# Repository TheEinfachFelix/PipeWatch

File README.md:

# PipeWatch

## Sensors

- MSU: LIS3DHTR 
- WS2812B
- Taster (Implementiert)
- Temp: 2x DS18B20(UMW) (Implementiert)
- ADC: ADS1115IDGSR (Implementiert)

## Todos

- Umrechnung der Werte in echte einheiten
- Dashboard für mehrere Geräte

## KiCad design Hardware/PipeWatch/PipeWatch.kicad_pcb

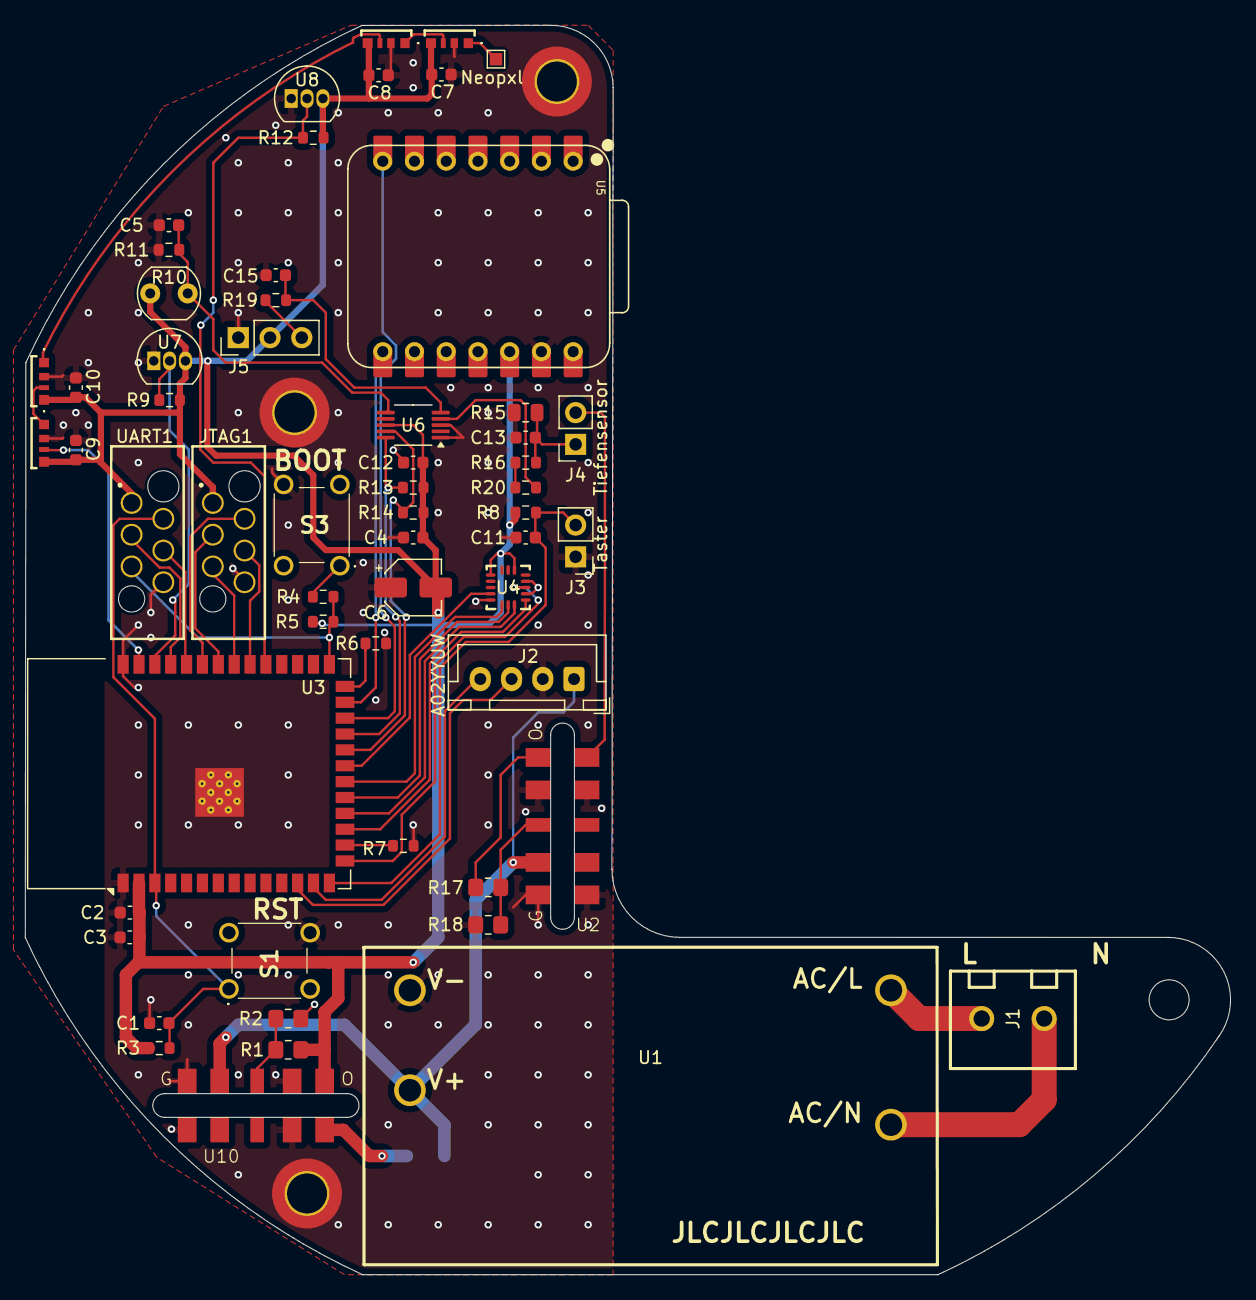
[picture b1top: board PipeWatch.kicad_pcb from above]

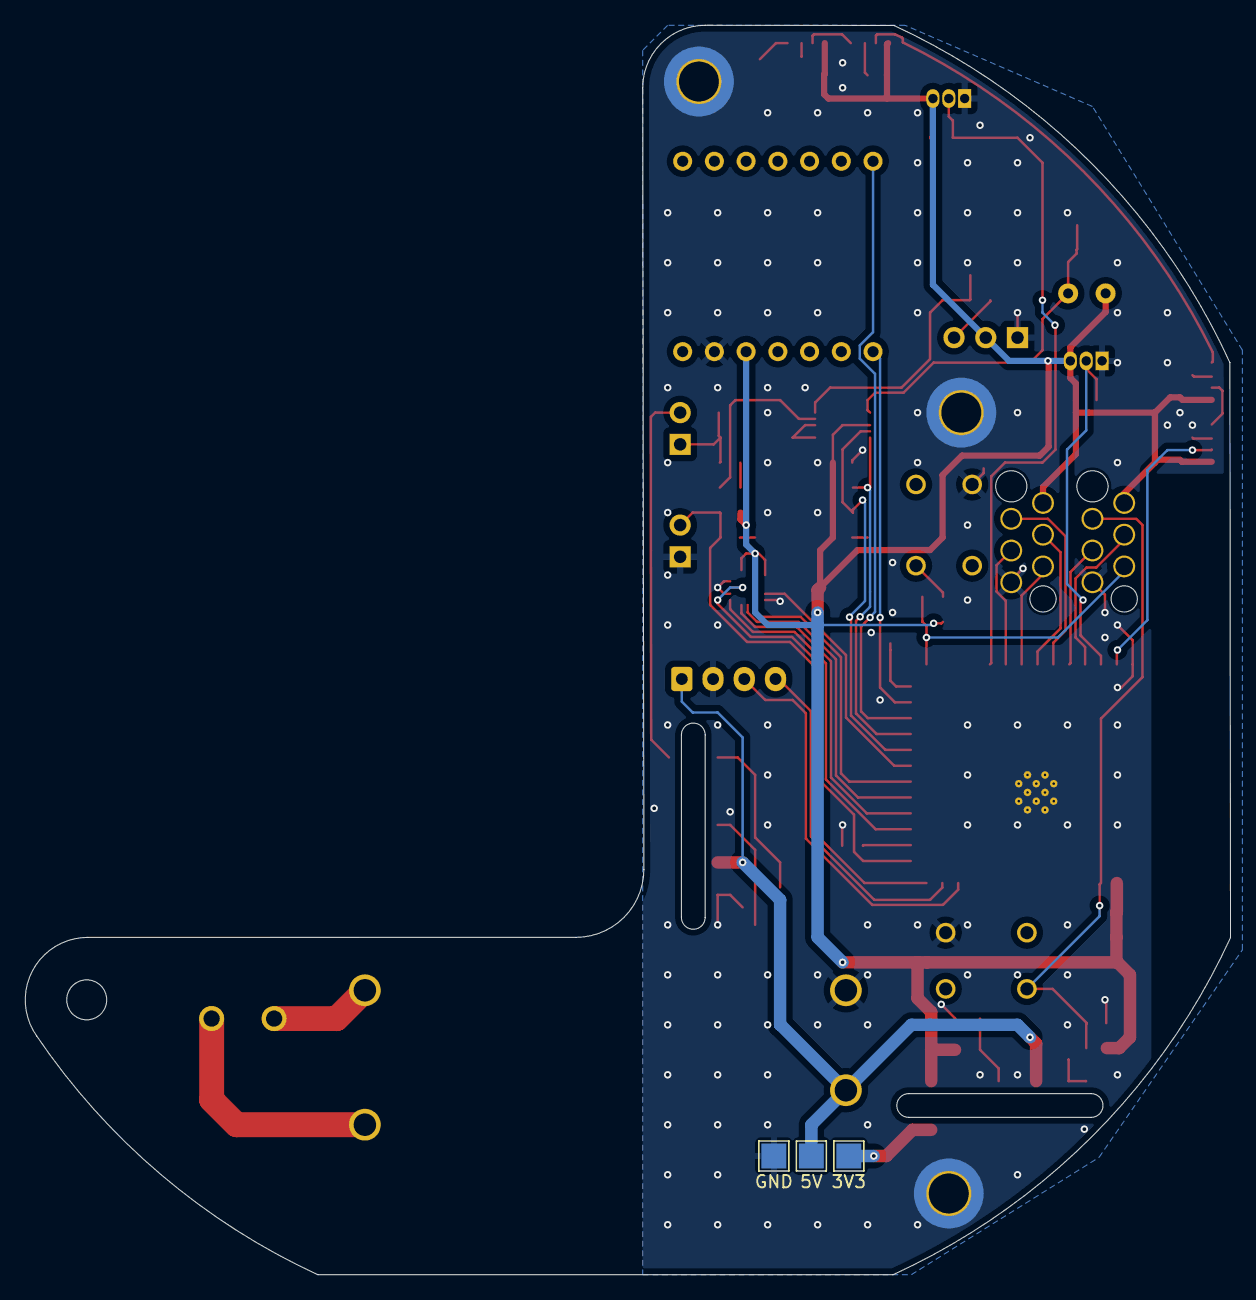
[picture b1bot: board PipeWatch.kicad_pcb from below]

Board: 2 copper layers, 96.5 x 100.0 mm, 64 parts (3 on the bottom side), 45 nets.

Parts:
C1, C2, C4, C7, C8, C9, C10, C11, C12: 100n; C_0603_1608Metric
C3: 22u; C_0603_1608Metric
C5, C13, C15: 10n; C_0603_1608Metric
C6: 10u; CP_Elec_4x5.8
D1, D2, D3, D4: WS2812B-2020; LED_4691_Neopixel_Edge
H1: MountingHole; MountingHole_3.2mm_M3
H2, H3, H4: MountingHole_Pad; MountingHole_3.2mm_M3_DIN965_Pad_TopBottom
J1: WJ126V-5.0-2P; CONN-TH_WJ126V-5.0-2P
J2: A02YYUW; JST_XH_B4B-XH-A_1x04_P2.50mm_Vertical
J3: Taster; PinHeader_1x02_P2.54mm_Vertical
J4: Tiefensensor; PinSocket_1x02_P2.54mm_Vertical
J5: Roter; PinHeader_1x03_P2.54mm_Vertical
JTAG1: 490107670612
R1, R2, R17, R18: R; R_0805_2012Metric_Pad1.20x1.40mm_HandSolder
R3, R5, R6, R7, R8, R13, R14, R16, R20: 10k; R_0603_1608Metric
R4, R19: 1k; R_0603_1608Metric
R9, R12: 4k7; R_0603_1608Metric
R10: R_Photo; R_LDR_5.0x4.1mm_P3mm_Vertical
R11: 10M; R_0603_1608Metric
R15: 150R; R_0805_2012Metric
S1, S3: TL1105AF160Q
TP1: Neopxl; TestPoint_Pad_1.0x1.0mm
TP2: 3V3; TestPoint_Pad_2.0x2.0mm
TP3: 5V; TestPoint_Pad_2.0x2.0mm
TP5: GND; TestPoint_Pad_2.0x2.0mm
U1: IRM-10-5_C20618064; PWRM-TH_4P-L45.7-W25.4-P8.0
U2, U10: VC-D-40-A
U3: ESP32-S3-WROOM-1-N16R8; ESP32-S3-WROOM-1
U4: LIS3DHTR_C15134; LGA-16_L3.0-W3.0-P0.50-TL
U5: XIAO-ESP32-S3-DIP; XIAO-ESP32S3-DIP
U6: ADS1115IDGS; VSSOP-10_3x3mm_P0.5mm
U7, U8: DS18B20; TO-92_Inline
UART1: 490107670612

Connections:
+3.3V: C2.2, C3.2, C4.2, C6.2, C7.2, C8.2, C9.2, C10.2, C12.2, D1.4 (VDD), D2.4 (VDD), D3.4 (VDD), D4.4 (VDD), J5.2, JTAG1.1, R1.1, R3.2, R5.1, R8.2, R9.1, R10.1, R12.1, R13.2, R14.2, TP2.1, U3.2 (3V3), U4.1 (VDD_IO), U4.14 (VDD), U5.12 (VCC_3V3), U6.8 (VDD), U7.3 (V_{DD}), U8.3 (V_{DD}), U10.4 (Vout), UART1.1
+5V: J2.1, TP3.1, U1.4 (+V), U2.1 (Vin), U10.1 (Vin)
+24V: J4.2, R17.1, U2.4 (Vout)
/ADC/PhotowiederstandInnen/OUT: C5.2, R10.2, R11.1, U6.6 (AIN2)
/ADC/Pressure/OUT: R20.1, U6.4 (AIN0)
/ADC/Roter/OUT: C15.1, R19.1, U6.5 (AIN1)
/ADC_SCL: R13.1, U3.23 (IO21), U6.10 (SCL)
/ADC_SDA: R14.1, U3.22 (IO14), U6.9 (SDA)
/MSU/CS: U3.18 (IO10), U4.8 (CS)
/MSU/INT2: U3.17 (IO9), U4.9 (INT2)
/MSU/SAO: U3.19 (IO11), U4.7 (SDO/SA0)
/MSU/SDI: U3.20 (IO12), U4.6 (SDA/SDI/SDO)
/MSU/SPC: U3.21 (IO13), U4.4 (SCL/SPC)
/MSU_INT1: U3.15 (IO3), U4.11 (INT1)
/TasterCall/OUT: C11.2, J3.2, R8.1, U3.14 (IO20)
/TemperaturOutside/OUT: R12.2, U3.31 (IO38), U8.2 (DQ)
/TemperaturPipe/OUT: R9.2, U3.38 (IO2), U7.2 (DQ)
/Uart2_RX: J2.3, U3.12 (IO8)
/Uart2_TX: J2.4, U3.13 (IO19)
/WS2812B1/Din: D2.3 (DIN), D3.1 (DOUT)
/WS2812B2/Din: D3.3 (DIN), D4.1 (DOUT)
/WS2812B Data: D4.3 (DIN), U3.39 (IO1)
/WS2812B/Din: D1.3 (DIN), D2.1 (DOUT)
/WS2812B/Dout: D1.1 (DOUT), TP1.1
GND: C1.1, C2.1, C3.1, C4.1, C5.1, C6.1, C7.1, C8.1, C9.1, C10.1, C11.1, C12.1, C13.2, C15.2, D1.2 (VSS), D2.2 (VSS), D3.2 (VSS), D4.2 (VSS), H2.1, H3.1, H4.1, J2.2, J3.1, J5.1, JTAG1.6, R2.2, R6.1, R7.1, R11.2, R15.2, R18.2, S1.4 (NO_2), S3.4 (NO_2), TP5.1, U1.3 (-V), U2.2 (GND), U3.1 (GND), U3.40 (GND), U3.41 (GND), U4.5 (GND), U4.10 (RES), U4.12 (GND), U5.13 (GND), U6.1 (ADDR), U6.3 (GND), U7.1 (GND), U8.1 (GND), U10.2 (GND), UART1.6
MTCK: JTAG1.4, U3.32 (IO39)
MTDI: JTAG1.3, U3.34 (IO41)
MTDO: JTAG1.5, U3.33 (IO40)
MTMS: JTAG1.2, U3.35 (IO42)
unnamed: J1.1, U1.1 (AC/N)
unnamed: J1.2, U1.2 (AC/L)
unnamed: C13.1, J4.1, R15.1, R16.2
unnamed: J5.3, R19.2
unnamed: R16.1, R20.2
unnamed: R4.2, S3.1 (COM_1)
unnamed: R17.2, R18.1, U2.3 (FB)
unnamed: R6.2, U3.26 (IO45)
unnamed: R7.2, U3.16 (IO46)
unnamed: U3.24 (IO47), U5.7 (U0TXD/D6/TX)
unnamed: U3.25 (IO48), U5.8 (U0RXD/D7/RX)
unnamed: R1.2, R2.1, U10.3 (FB)
OI0: R4.1, R5.2, U3.27 (IO0), UART1.5
RST: C1.2, R3.1, S1.1 (COM_1), U3.3 (EN), UART1.2
RX0: U3.36 (RXD0), UART1.4
TX0: U3.37 (TXD0), UART1.3

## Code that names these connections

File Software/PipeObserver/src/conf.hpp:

#pragma once

// ADC
#define ADC_SDA_PIN 14
#define ADC_SCL_PIN 21
#define ADC_CH_Pressure 0
#define ADC_CH_WaterLvl 1
#define ADC_CH_Photores 2
#define ADC_CH_NC 3

// Temperature Sensors
#define INNER_TEMP_PIN 2   // GPIO pin for inner temperature sensor
#define OUTER_TEMP_PIN 38  // GPIO pin for outer temperature sensor
#define TEMP_RESOLUTION 10 // 9, 10, 11, or 12 bits

// Button
#define BUTTON_PIN 20 // GPIO pin for button

// LED Strip
#define LED_PIN 1        // GPIO pin for LED strip
#define NUM_LEDS 4      // Number of LEDs in the strip

// MSU
#define MSU_INT1_PIN 3 // GPIO pin for MSU INT1
#define MSU_INT2_PIN 9 // GPIO pin for MSU INT2
#define MSU_CS_PIN 10  // GPIO pin for MSU CS
#define MSU_SAO_PIN 11 // GPIO pin for MSU SAO
#define MSU_SDI_PIN 12 // GPIO pin for MSU SDI
#define MSU_SPC_PIN 13 // GPIO pin for MSU SPC

// Json
#define JSON_DEVICE_NAME "ESP32-S3-01"
#define JSON_MSG_TYPE_ERROR "ERROR"
#define JSON_MSG_TYPE_DATA "DATA"
#define JSON_VERSION 1

// Status
#define STATUS_RUN "RUN"
#define STATUS_ERROR "Error"
#define STATUS_START "Startup"

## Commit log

2025-08-31 started the scematic
2025-09-10 tweeked the Layout
2025-09-11 Started implementing the accelerometer
2025-09-11 added Binky parts and a load of 3d references
2025-09-16 some changes
2025-09-17 Added Ten Sensor
2025-09-18 added adc
2025-09-20 Started laying traces
2025-09-21 Final Version (Ordered it)
2025-09-24 Changed the scematic page Labeling
2025-10-08 added Pipe Observer Proj
2025-10-08 added libs
2025-10-08 added temp Sensor
2025-10-08 added adc and conf
2025-10-08 started with msu added all pins
2025-10-12 most of is working
2025-10-12 stuff now working
2025-10-12 working msu
2026-02-13 nodered spawning is now partialy working
2026-02-20 Flows now get imported
2026-02-20 Started adding influx
2026-02-27 flow can recive data
2026-02-27 Implemented unbuffered log sending
2026-02-27 implemented MSU
2026-02-27 added test if adc is running
2026-03-06 test script
2026-03-15 done some stuff
2026-03-15 added Grafana
2026-03-15 added notes tweeked the dachboard
2026-03-19 Added alerting
2026-03-20 updated text
